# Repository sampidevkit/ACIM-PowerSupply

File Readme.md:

# AC INDUCTION MOTOR - POWER SUPPLY BOARD V1

## 1. Schematic

[Revision 1.0](Production\Sch\HW.ACIM-PSU.pdf).

## 2. PCB

.png)

.png)

.png)

.png)

.png)

.png)

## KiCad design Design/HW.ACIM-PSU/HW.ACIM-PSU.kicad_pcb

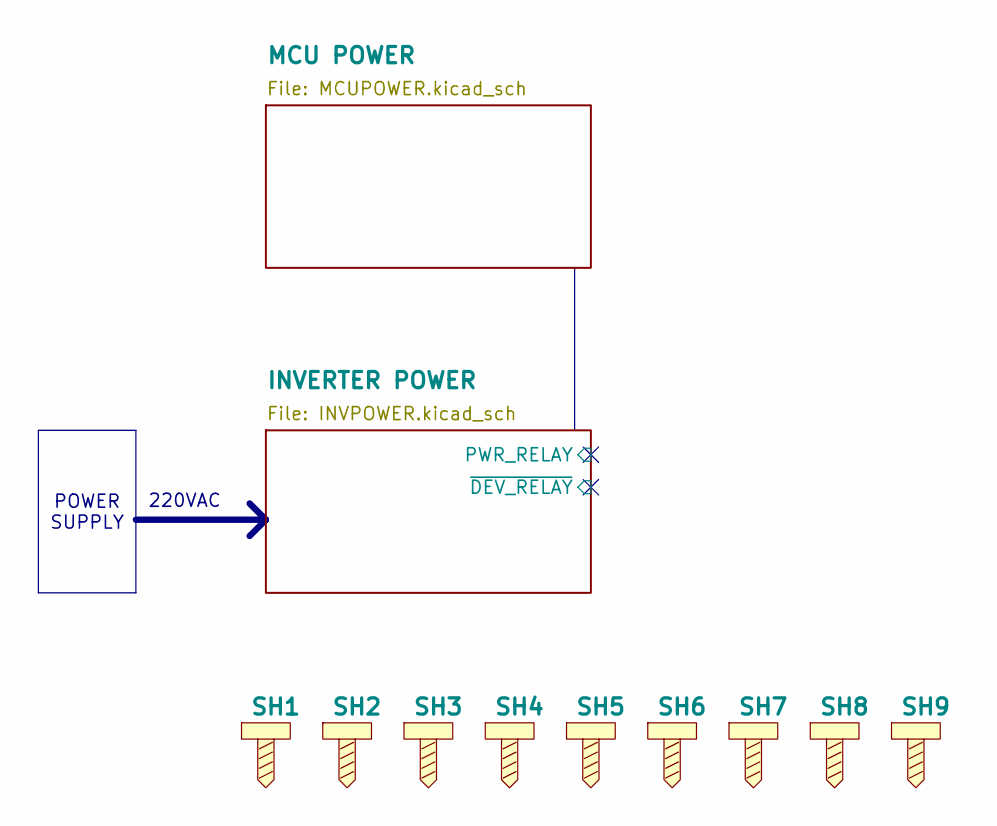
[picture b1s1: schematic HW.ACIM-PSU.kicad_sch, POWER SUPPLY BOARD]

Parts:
SH1, SH2, SH3, SH4, SH5, SH6, SH7, SH8, SH9: SCREW HOLDER; SCREWHOLE-2.5M

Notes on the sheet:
POWER SUPPLY
220VAC

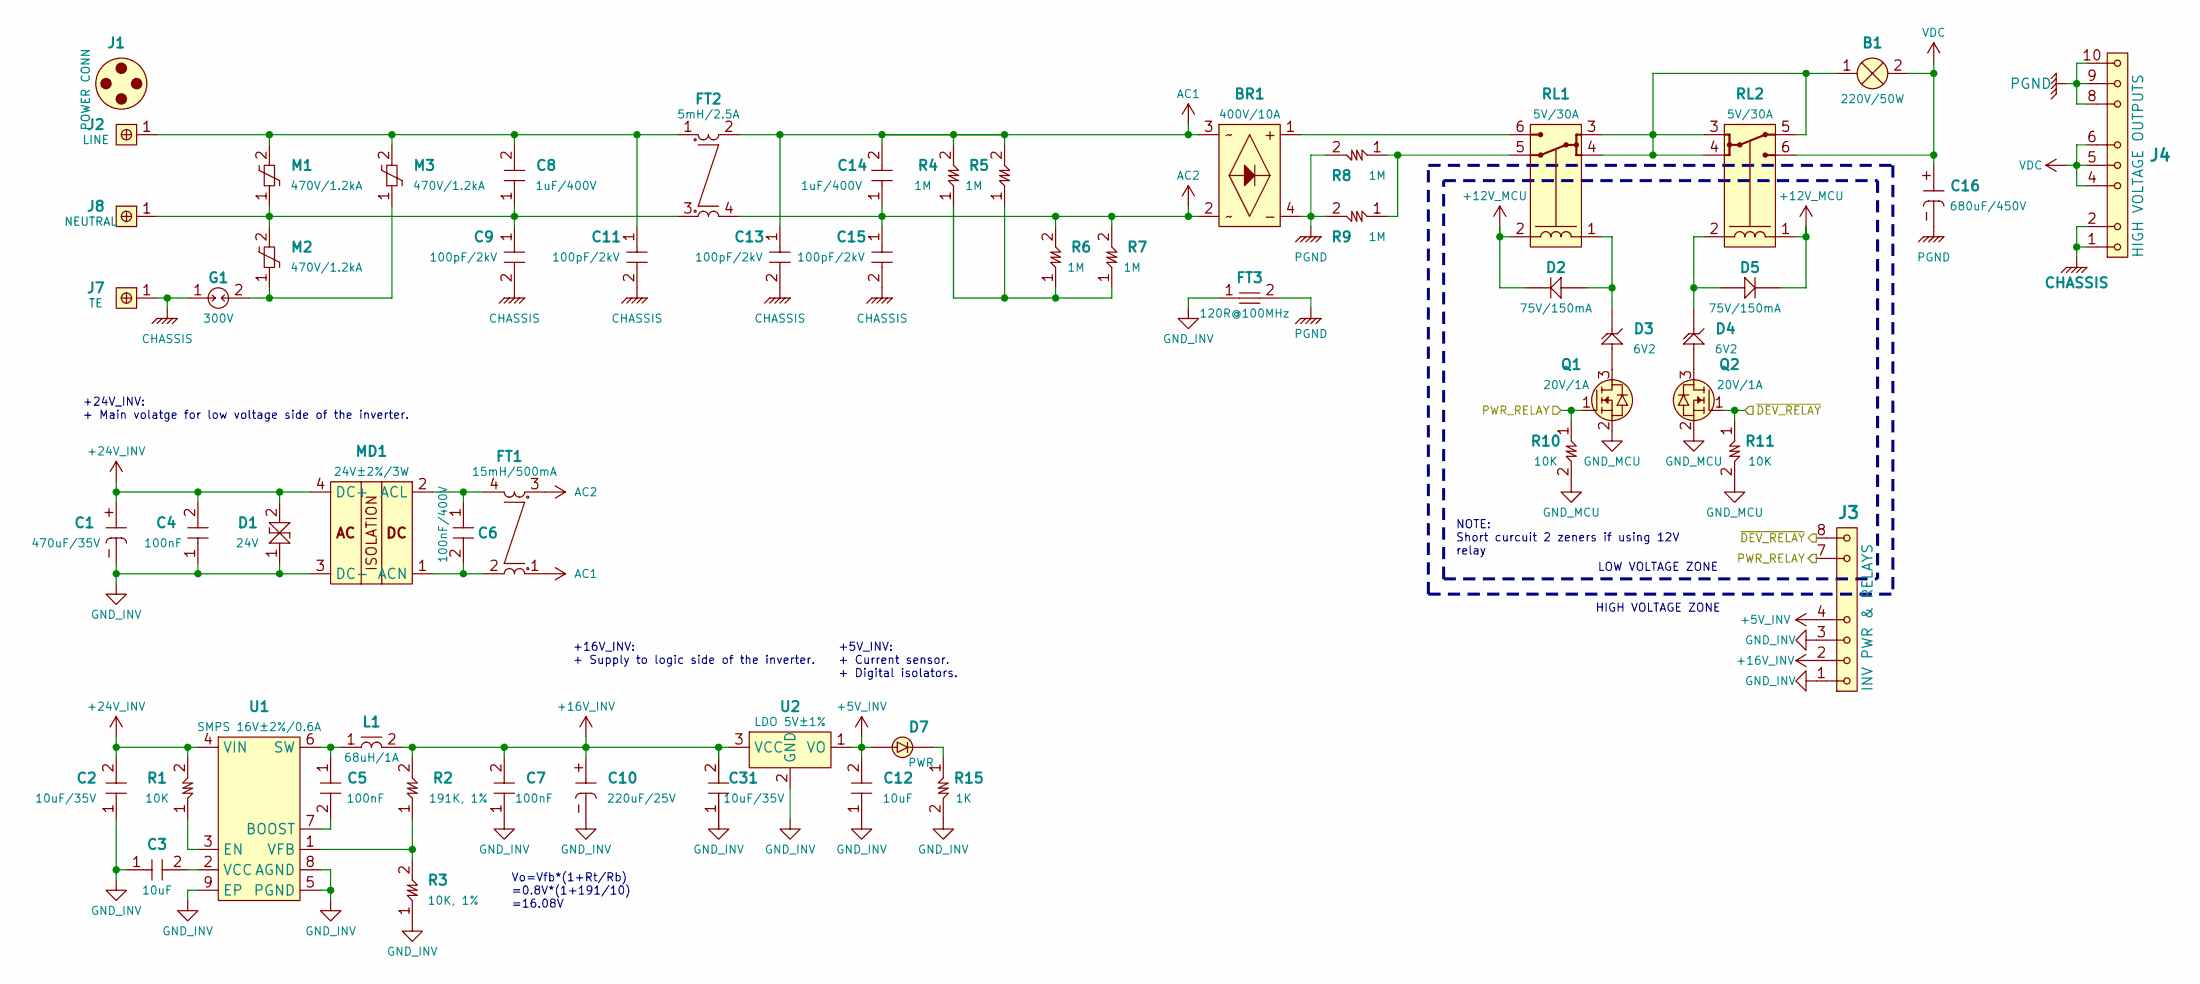
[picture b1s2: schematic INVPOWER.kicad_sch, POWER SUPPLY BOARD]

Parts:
B1: 220V/50W; LAMP_6.35MM
BR1: 400V/10A; GBJ25xx
C1: 470uF/35V; CAP_ELEC-10.3x10.3-DIA10
C2, C31: 10uF/35V; CAP1206
C3, C12: 10uF; CAP0603
C4, C5, C7: 100nF; CAP0603
C6: 100nF/400V; CAP_FILM_6.0x12.0x12.5-P10
C8, C14: 1uF/400V; ECWFE2W105
C9, C11, C13, C15: 100pF/2kV; CAP1206
C10: 220uF/25V; CAP_ELEC-8.3x8.3-DIA8.0
C16: 680uF/450V; ESMQ451VSN681MA50S
D1: 24V; DO-214AA-12
D2, D5: 75V/150mA; SOD-323
D3, D4: 6V2; SOD80C-LL34
D7: PWR; LED0603
FT1: 15mH/500mA; EE8.3
FT2: 5mH/2.5A; IND-SQ1010
FT3: 120R@100MHz; FT0603
G1: 300V; GDT1812_3532
J1: POWER CONN
J2: LINE; QC-6.3
J3: INV PWR & RELAYS; HDM1x8x2.54_TH_RA
J4: HIGH VOLTAGE OUTPUTS; HDF1x10x2.54_TH_RA
J7: TE; QC-6.3
J8: NEUTRAL; QC-6.3
L1: 68uH/1A; IND-8D43-8045
M1, M2, M3: 470V/1.2kA; MOV5MM
MD1: 24V±2%/3W; HLK-PMxx
Q1, Q2: 20V/1A; SOT23
R1, R10, R11: 10K; RES0603
R2: 191K, 1%; RES0603
R3: 10K, 1%; RES0603
R4, R5, R6, R7, R8, R9: 1M; RES1206
R15: 1K; RES0603
RL1, RL2: 5V/30A; SLA-12VDC-SL-C
U1: SMPS 16V±2%/0.6A; TDFN8_2x3_MCHP
U2: LDO 5V±1%; SOT-89

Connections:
+5V_INV: C12.2, D7.A, J3.4, U2.1 (VO)
+12V_MCU: D2.K, D5.K, RL1.2 (COIL2), RL2.1 (COIL1); also elsewhere on the board
+16V_INV: C7.2, C10.+, C31.2, J3.2, L1.2, R2.2, U2.3 (VCC)
+24V_INV: C1.+, C2.2, C4.2, D1.2 (A2), MD1.4 (DC+), R1.2, U1.4 (VIN)
/INVERTER POWER/PWR_RELAY: J3.7, Q1.1 (G), R10.1
/INVERTER POWER/~DEV_RELAY: J3.8, Q2.1 (G), R11.1
AC1: BR1.3 (AC2), C13.1, C14.2, FT1.1, FT2.2, R4.2, R5.2; also elsewhere on the board
AC2: BR1.2 (AC1), C14.1, C15.1, FT1.3, FT2.4, R6.2, R7.2; also elsewhere on the board
CHASSIS: C9.2, C11.2, C13.2, C15.2, G1.1, J4.1, J4.2, J7.1
GND_INV: C1.-, C2.1, C3.1, C4.1, C7.1, C10.-, C12.1, C31.1, D1.1 (A1), FT3.1, J3.1, J3.3, MD1.3 (DC-), R3.1, R15.2, U1.5 (PGND), U1.8 (AGND), U1.9 (EP), U2.2 (GND)
GND_MCU: Q1.2 (S), Q2.2 (S), R10.2, R11.2; also elsewhere on the board
unnamed: BR1.1 (DC+), RL1.6 (NO)
unnamed: C8.1, C9.1, FT2.3, J8.1, M1.1, M2.2
unnamed: C8.2, C11.1, FT2.1, J2.1, M1.2, M3.2
unnamed: D7.K, R15.1
unnamed: G1.2, M2.1, M3.1
unnamed: C6.1, FT1.4, MD1.2 (ACL)
unnamed: C6.2, FT1.2, MD1.1 (ACN)
unnamed: D3.A, Q1.3 (D)
unnamed: D4.A, Q2.3 (D)
unnamed: R4.1, R5.1, R6.1, R7.1
unnamed: D2.A, D3.K, RL1.1 (COIL1)
unnamed: R8.1, R9.1, RL1.5 (NC)
unnamed: D4.K, D5.A, RL2.2 (COIL2)
unnamed: B1.1, RL1.3 (COM), RL1.4 (COM), RL2.3 (COM), RL2.4 (COM), RL2.5 (NC)
unnamed: C5.2, U1.7 (BOOST)
unnamed: R1.1, U1.3 (EN)
unnamed: C5.1, L1.1, U1.6 (SW)
unnamed: C3.2, U1.2 (VCC)
unnamed: R2.1, R3.2, U1.1 (VFB)
PGND: BR1.4 (DC-), C16.-, FT3.2, J4.8, J4.9, J4.10, R8.2, R9.2
VDC: B1.2, C16.+, J4.4, J4.5, J4.6, RL2.6 (NO)

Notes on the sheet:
+24V_INV: + Main volatge for low voltage side of the inverter.
+5V_INV: + Current sensor. + Digital isolators.
+16V_INV: + Supply to logic side of the inverter.
NOTE: Short curcuit 2 zeners if using 12V relay
Vo=Vfb*(1+Rt/Rb) =0.8V*(1+191/10) =16.08V
HIGH VOLTAGE ZONE
LOW VOLTAGE ZONE

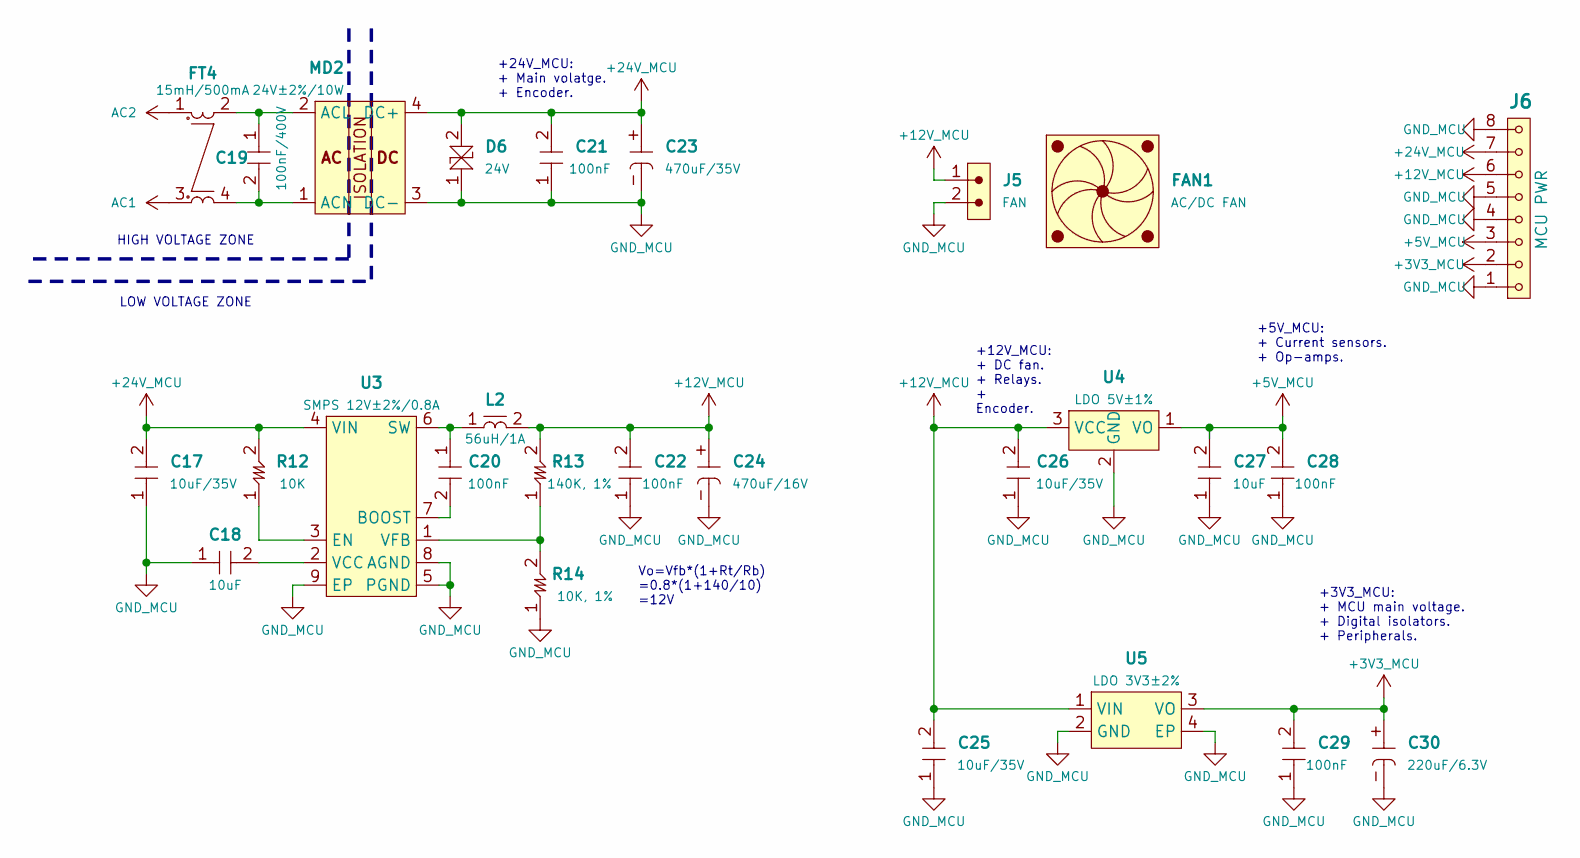
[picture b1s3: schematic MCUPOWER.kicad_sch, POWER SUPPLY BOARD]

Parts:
C17, C25, C26: 10uF/35V; CAP1206
C18, C27: 10uF; CAP0603
C19: 100nF/400V; CAP_FILM_6.0x12.0x12.5-P10
C20, C21, C22, C28, C29: 100nF; CAP0603
C23: 470uF/35V; CAP_ELEC-10.3x10.3-DIA10
C24: 470uF/16V; CAP_ELEC-8.3x8.3-DIA8.0
C30: 220uF/6.3V; CAP1411
D6: 24V; DO-214AA-12
FAN1: AC/DC FAN
FT4: 15mH/500mA; EE8.3
J5: FAN; HDM-2x2.54-TH
J6: MCU PWR; HDM1x8x2.54_TH_RA
L2: 56uH/1A; IND-8D43-8045
MD2: 24V±2%/10W; HLK-10M
R12: 10K; RES0603
R13: 140K, 1%; RES0603
R14: 10K, 1%; RES0603
U3: SMPS 12V±2%/0.8A; TDFN8_2x3_MCHP
U4: LDO 5V±1%; SOT-89
U5: LDO 3V3±2%; SOT-223-3

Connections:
+3V3_MCU: C29.2, C30.+, J6.2, U5.3 (VO)
+5V_MCU: C27.2, C28.2, J6.3, U4.1 (VO)
+12V_MCU: C22.2, C24.+, C25.2, C26.2, J5.1, J6.6, L2.2, R13.2, U4.3 (VCC), U5.1 (VIN); also elsewhere on the board
+24V_MCU: C17.2, C21.2, C23.+, D6.2 (A2), J6.7, MD2.4 (DC+), R12.2, U3.4 (VIN)
AC1: FT4.3; also elsewhere on the board
AC2: FT4.1; also elsewhere on the board
GND_MCU: C17.1, C18.1, C21.1, C22.1, C23.-, C24.-, C25.1, C26.1, C27.1, C28.1, C29.1, C30.-, D6.1 (A1), J5.2, J6.1, J6.4, J6.5, J6.8, MD2.3 (DC-), R14.1, U3.5 (PGND), U3.8 (AGND), U3.9 (EP), U4.2 (GND), U5.2 (GND), U5.4 (EP); also elsewhere on the board
unnamed: C19.1, FT4.2, MD2.2 (ACL)
unnamed: C19.2, FT4.4, MD2.1 (ACN)
unnamed: C20.2, U3.7 (BOOST)
unnamed: R12.1, U3.3 (EN)
unnamed: C20.1, L2.1, U3.6 (SW)
unnamed: C18.2, U3.2 (VCC)
unnamed: R13.1, R14.2, U3.1 (VFB)

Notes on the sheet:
+12V_MCU: + DC fan. + Relays. + Encoder.
+24V_MCU: + Main volatge. + Encoder.
Vo=Vfb*(1+Rt/Rb) =0.8*(1+140/10) =12V
+5V_MCU: + Current sensors. + Op-amps.
+3V3_MCU: + MCU main voltage. + Digital isolators. + Peripherals.
LOW VOLTAGE ZONE
HIGH VOLTAGE ZONE

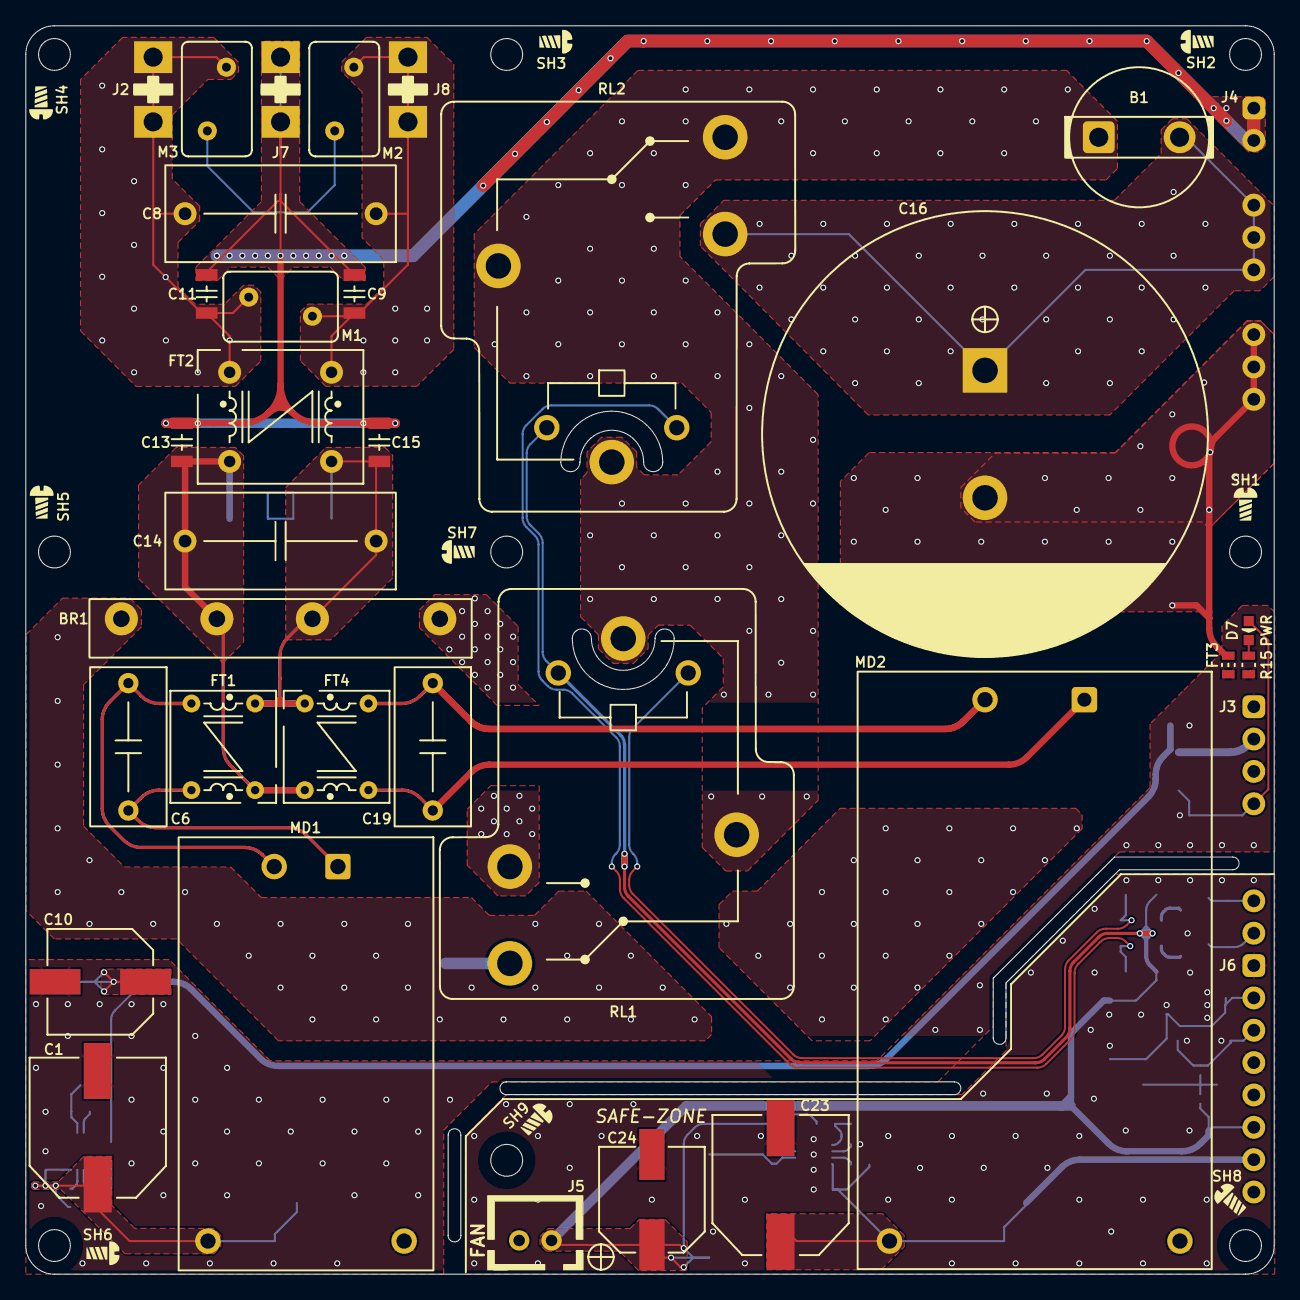
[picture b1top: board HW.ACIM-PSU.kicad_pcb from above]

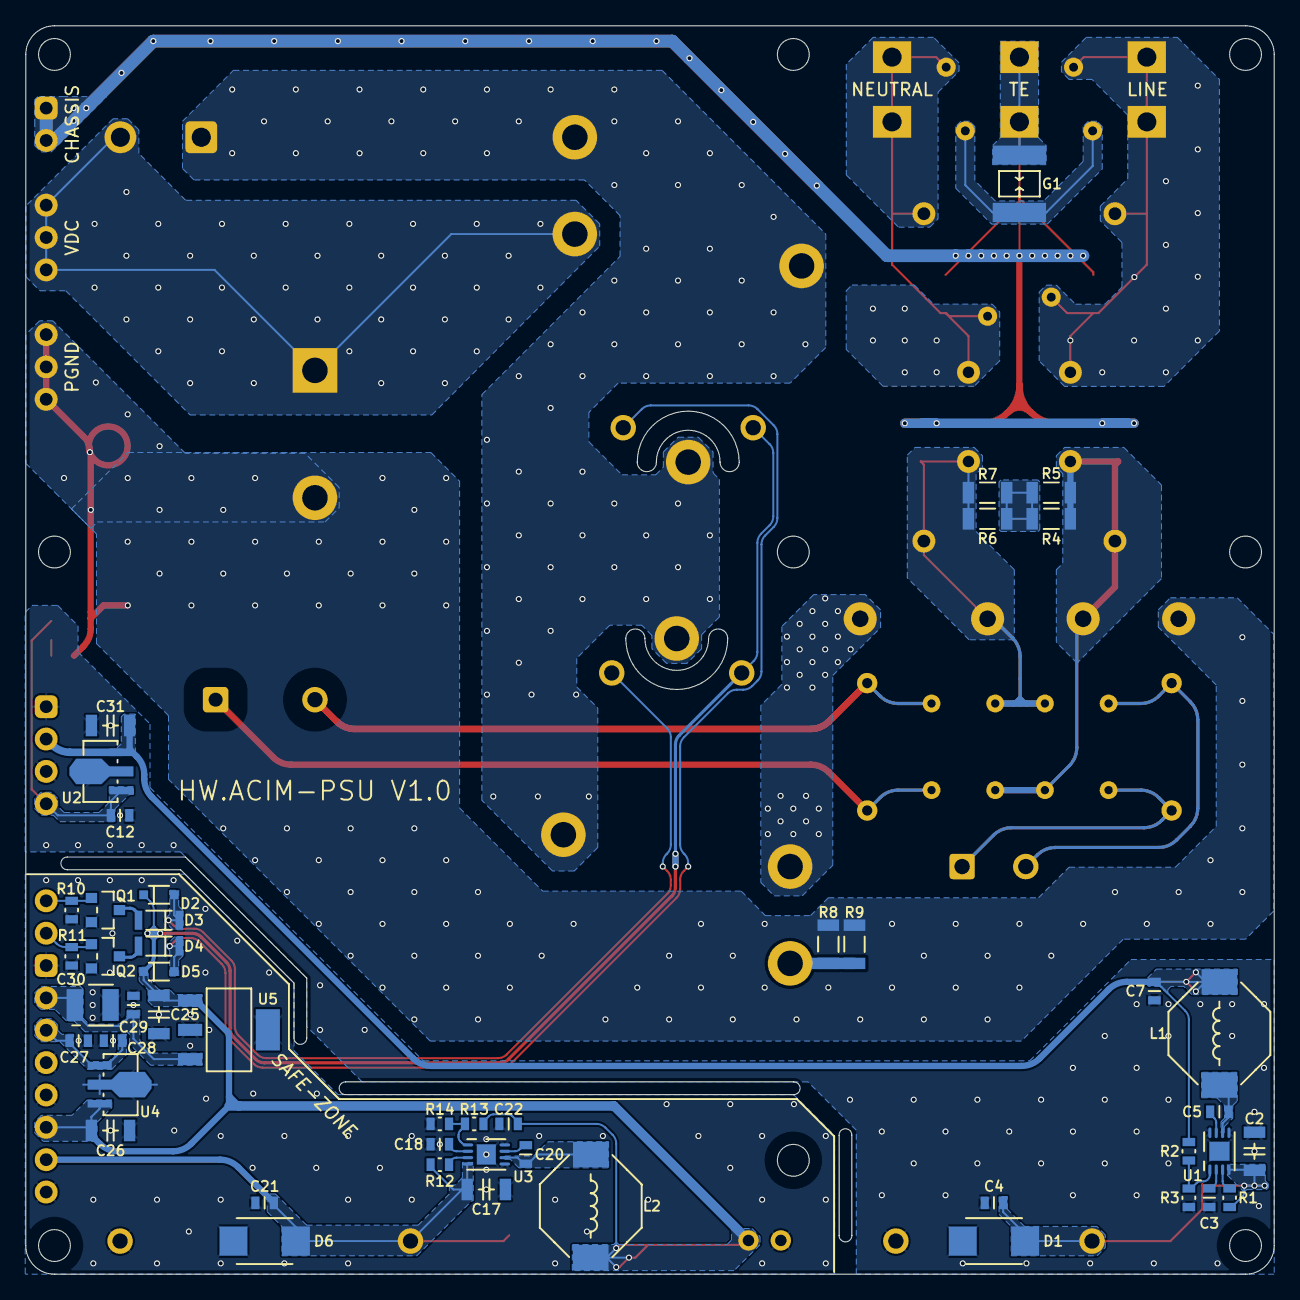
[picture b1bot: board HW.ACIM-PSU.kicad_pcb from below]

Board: 4 copper layers, 98.0 x 98.0 mm, 92 parts (48 on the bottom side), 42 nets.

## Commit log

2024-09-25 Initialize
2024-09-25 V0 production files
2024-09-26 V0 production files update 1
2024-10-10 V0 production files update 2
2024-12-22 V1 schematic
2024-12-23 V1 layout
2024-12-29 V1 layout update 1
2025-01-13 V1 layout update 2
2025-01-14 V1 layout update 3
2025-01-15 V1 layout update 4
2025-01-18 V1 layout update 5
2025-01-19 HW.ACIM-PSU_REV1.0 production
2025-01-19 HW.ACIM-PSU_REV1.0 update info
